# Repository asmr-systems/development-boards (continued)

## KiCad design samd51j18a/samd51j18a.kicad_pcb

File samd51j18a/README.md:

# SAMD51J18A Development Board

# Physical MCU Package
* 64 Pins
* 256KB ROM
* TQFP

## Questions
* **do we need an external clock (XIN32/XOUT32)?**: it looks like the schematics in the references include an external crystal oscillator clock.
 * looks like this is for a external 32K crystal oscillator clock for the real-time clock. (see clock notes)
* **what is the relationship between VDDIO, VDDCORE, and VDDANA?**: it looks like from the schematics in the references that there are related somehow.
 * we can refer to the power supply section in the datasheet.

## USB
supports USB 2.0 interface (host & device)
For USB 3 hardware (which is what we are using), there are two pins CC1 and CC2 which are for negotiating power delivery over USB. Note, that this negotiation will only happen if both host and device are using USB C.
Looking at the USB C power delivery overview in the references (page 8/17), we can see that for power sinks (which is what we are), we need to include a 5.1K pull-down resistor on both CC1 and CC2.
### 22 Ohm D-/D+ Termination Resistors
in some schematics, the D-/D+ transmission lines include series 22 Ohm resistors. This is because the USB standard specifies that the signal to ground impedance is 30 ohms. So, we need to do some impedance matching to avoid signal integrity problems (see Why USB Data Series Resistors).
This is something that we need to know about the device we are using. In the SAMD51 Data sheet it says " On-Chip USB serial resistors", which means we DON'T have to add these externally.
### Pinout
Pin 45 (PA24) has USB/DM (D-)
Pin 46 (PA25) has USB/DP (D+)

## sd card
### Pinout
Pin 15 (PA06) has SDHC0/SDCD (card detect)
Pin 17 (PA08) has SDHC0/SDCMD
Pin 18 (PA09) has SDHC0/SDDAT[0]
Pin 19 (PA10) has SDHC0/SDDAT[1]
Pin 20 (PA11) has SDHC0/SDDAT[2]
Pin 23 (PB10) has SDHC0/SDDAT[3]
Pin 24 (PB11) has SDHC0/SDCK

## Cortex_CM4
## Pinout
Pin 57 (PA30) has SWCLK
Pin 58 (PA31) has SWDIO

## Power Supply Considerations
On page 2097 of the SAMD51 Data sheet, there is a schematic checklist and it shows schematics for the power supply pins.
We want Linear Mode only, so thats what we will model it after.
It looks like they include an inductor for doing some power supply filtering. In the schematics for other samd51 boards it says "FB - 30 Ohms" above the inductor. It seems that this means "Ferrite Beads" which are often used for power supplying filtering, they act like inductors (see org notes on ferrite beads).

## Clocks
it is recommended to use an external crystal oscillator since it is more accurate than the internal RC oscillator. It seems like you can provide an external 32K crystal oscillator which can then drive the DFLL or DPLL to achieve higher clock speeds up to 120Mhz.

## References
* [SAM D5x/E5x Data Sheet](https://www.mouser.com/datasheet/2/268/60001507A-1130176.pdf)
* [SAMD51 SparkFun Thing Plus Schematic](https://cdn.sparkfun.com/assets/8/2/1/d/f/SAMD51_Thing_Plus_v10.pdf)
* [SAMD51 SparkFun MicroMod Board Schematic](https://cdn.sparkfun.com/assets/1/d/3/e/b/SparkFun_MicroMod_SAMD51_Processor_Board_Schematic.pdf)
* [USB C & Power Delivery Overview](https://www.st.com/resource/en/technical_article/dm00496853-overview-of-usb-type-c-and-power-delivery-technologies-stmicroelectronics.pdf)
* [Why USB Data Series Resistors?](https://www.eevblog.com/forum/projects/why-usb-data-series-resistors/msg440967/#msg440967)

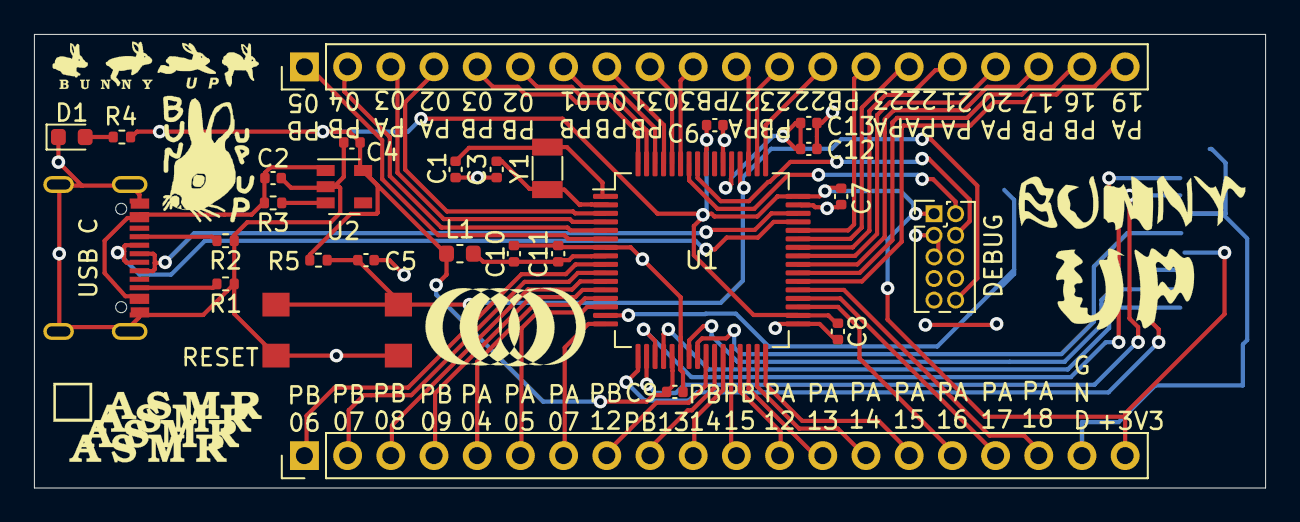
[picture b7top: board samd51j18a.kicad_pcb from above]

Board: 2 copper layers, 72.4 x 26.7 mm, 29 parts (1 on the bottom side), 61 nets.

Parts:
C1, C3: 15pF; C_0402_1005Metric
C2, C5, C6, C7, C8, C9, C11, C13: 0.1uF; C_0402_1005Metric
C4: 1.0uF; C_0402_1005Metric
C10: 10uF; C_0402_1005Metric
C12: 4.7uF; C_0402_1005Metric
D1: LED; LED_0603_1608Metric
DEBUG: Conn_ARM_JTAG_SWD_10; PinHeader_2x05_P1.27mm_Vertical
J1, J4: Conn_01x20_Male; PinHeader_1x20_P2.54mm_Vertical
L1: FB - 30Ohm; L_0603_1608Metric
MICRO SD: Micro_SD_Card_Det; microSD_GCT_MEM2061-01-188-00
R1, R2: 5.1K; R_0402_1005Metric
R3: 10K; R_0402_1005Metric
R4: 100; R_0402_1005Metric
R5: 4.7K; R_0402_1005Metric
RESET: SW_SPST; SW_Push_TL3305
U1: ATSAMD51J18A-A; TQFP-64_10x10mm_P0.5mm
U2: NJM2866F33; SOT-23-5
USB C: USB_C_Receptacle_USB2.0; USB_C_Receptacle_GCT_USB4105
Y1: 32.768kHz; Crystal_SMD_3215-2Pin_3.2x1.5mm

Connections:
+3V3: C4.1, C6.1, C7.1, C8.1, C9.1, DEBUG.1, J1.20, L1.1, MICRO SD.4, R4.1, R5.1, U1.21, U1.34, U1.48, U1.56, U2.5
D+: U1.46, USB C.A6, USB C.B6
D-: U1.45, USB C.A7, USB C.B7
GND: C1.2, C2.2, C3.2, C4.2, C5.2, C6.2, C7.2, C8.2, C9.2, C10.2, C11.2, C12.2, C13.2, D1.1, DEBUG.3, DEBUG.5, J1.19, MICRO SD.6, MICRO SD.11, R1.1, R2.1, RESET.2, U1.7, U1.22, U1.33, U1.47, U1.54, U2.2, USB C.A1, USB C.A12, USB C.B1, USB C.B12, USB C.S1
unnamed: D1.2, R4.2
unnamed: R2.2, USB C.A5
unnamed: R1.2, USB C.B5
unnamed: R3.1, U2.3
PA02: J4.4, U1.3
PA03: J4.3, U1.4
PA04: J1.5, U1.13
PA05: J1.6, U1.14
PA07: J1.7, U1.16
PA12: J1.12, U1.29
PA13: J1.13, U1.30
PA14: J1.14, U1.31
PA15: J1.15, U1.32
PA16: J1.16, U1.35
PA17: J1.17, U1.36
PA18: J1.18, U1.37
PA19: J4.20, U1.38
PA20: J4.17, U1.41
PA21: J4.16, U1.42
PA22: J4.15, U1.43
PA23: J4.14, U1.44
PA27: J4.11, U1.51
PB00: J4.8, U1.61
PB01: J4.7, U1.62
PB02: J4.6, U1.63
PB03: J4.5, U1.64
PB04: J4.2, U1.5
PB05: J4.1, U1.6
PB06: J1.1, U1.9
PB07: J1.2, U1.10
PB08: J1.3, U1.11
PB09: J1.4, U1.12
PB12: J1.8, U1.25
PB13: J1.9, U1.26
PB14: J1.10, U1.27
PB15: J1.11, U1.28
PB16: J4.19, U1.39
PB17: J4.18, U1.40
PB22: J4.13, U1.49
PB23: J4.12, U1.50
PB30: J4.10, U1.59
PB31: J4.9, U1.60
RESET: C5.1, DEBUG.10, R5.2, RESET.1, U1.52
SDCD: MICRO SD.9, MICRO SD.10, U1.15
SDCK: MICRO SD.5, U1.24
SDCMD: MICRO SD.3, U1.17
SDDAT[0]: MICRO SD.7, U1.18
SDDAT[1]: MICRO SD.8, U1.19
SDDAT[2]: MICRO SD.1, U1.20
SDDAT[3]: MICRO SD.2, U1.23
SWCLK: DEBUG.4, U1.57
SWDIO: DEBUG.2, U1.58
VCC: C12.1, C13.1, U1.53
VDD: C2.1, R3.2, U2.1, USB C.A4, USB C.A9, USB C.B4, USB C.B9
VDDA: C10.1, C11.1, L1.2, U1.8
XIN32: C1.1, U1.1, Y1.1
XOUT32: C3.1, U1.2, Y1.2
